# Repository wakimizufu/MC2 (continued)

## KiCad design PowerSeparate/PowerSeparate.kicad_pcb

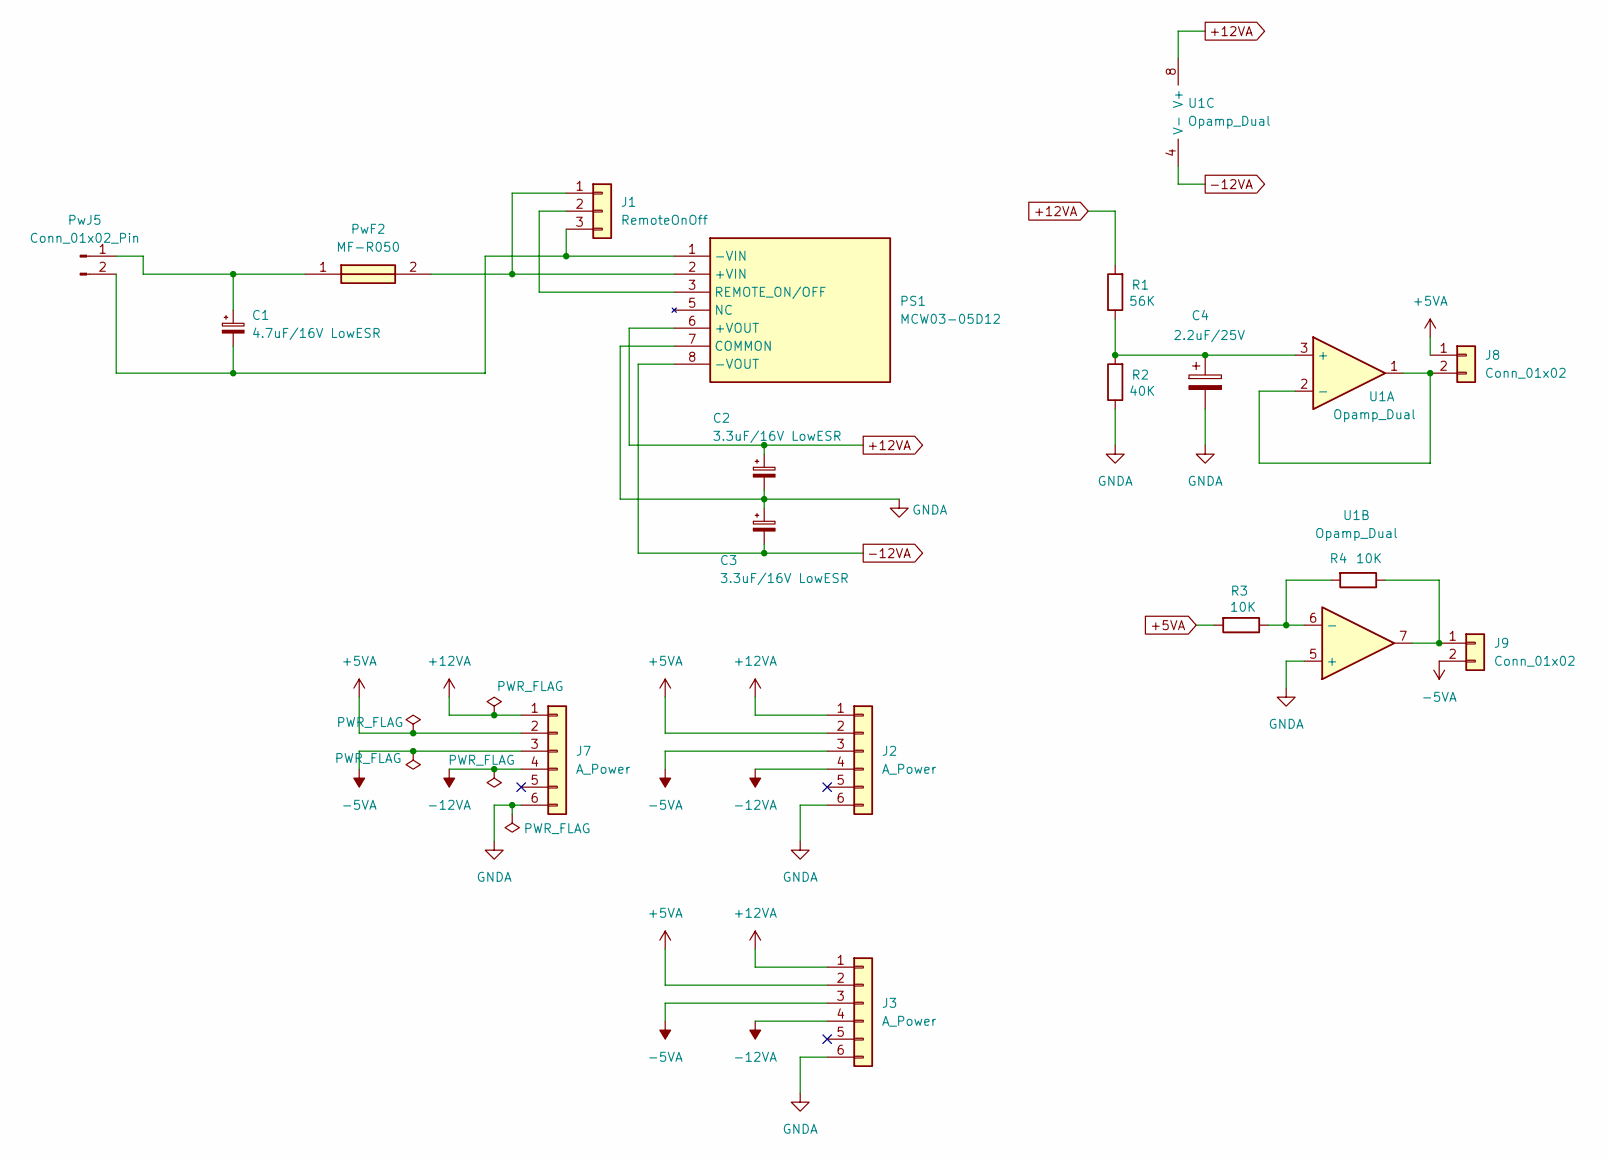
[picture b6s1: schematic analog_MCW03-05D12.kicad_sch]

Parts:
C1: 4.7uF/16V LowESR; CP_Radial_D5.0mm_P2.50mm
C2, C3: 3.3uF/16V LowESR; CP_Radial_D5.0mm_P2.50mm
C4: 2.2uF/25V; CP_Radial_D5.0mm_P2.50mm
J1: RemoteOnOff; PinSocket_1x03_P2.54mm_Vertical
J2, J3, J7: A_Power; PinHeader_1x06_P2.54mm_Vertical
J8, J9: Conn_01x02; PinHeader_1x02_P2.54mm_Vertical
PS1: MCW03-05D12; MCW0305D12; Manufacturer_Part_Number MCW03-05D12
PwF2: MF-R050; MFR050; Manufacturer_Part_Number MF-R050; Mouser Part Number 652-MFR050
PwJ5: Conn_01x02_Pin; PinHeader_1x02_P2.54mm_Vertical
R1: 56K; R_Axial_DIN0207_L6.3mm_D2.5mm_P2.54mm_Vertical
R2: 40K; R_Axial_DIN0207_L6.3mm_D2.5mm_P2.54mm_Vertical
R3, R4: 10K; R_Axial_DIN0207_L6.3mm_D2.5mm_P2.54mm_Vertical
U1: Opamp_Dual; SOIC-8_3.9x4.9mm_P1.27mm

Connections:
+5VA: J2.2, J3.2, J7.2, J8.1, R3.2
+12VA: C2.1, J2.1, J3.1, J7.1, PS1.6 (+VOUT), R1.2, U1.8 (V+)
-5VA: J2.3, J3.3, J7.3, J9.2
-12VA: C3.2, J2.4, J3.4, J7.4, PS1.8 (-VOUT), U1.4 (V-)
GNDA: C2.2, C3.1, C4.2, J2.6, J3.6, J7.6, PS1.7 (COMMON), R2.1, U1.5 (+)
unnamed: J1.1, PS1.2 (+VIN), PwF2.2
unnamed: J1.2, PS1.3 (REMOTE_ON/OFF)
unnamed: C1.2, J1.3, PS1.1 (-VIN), PwJ5.2
unnamed: J8.2, U1.1, U1.2 (-)
unnamed: J9.1, R4.1, U1.7
unnamed: C1.1, PwF2.1, PwJ5.1
unnamed: C4.1, R1.1, R2.2, U1.3 (+)
unnamed: R3.1, R4.2, U1.6 (-)

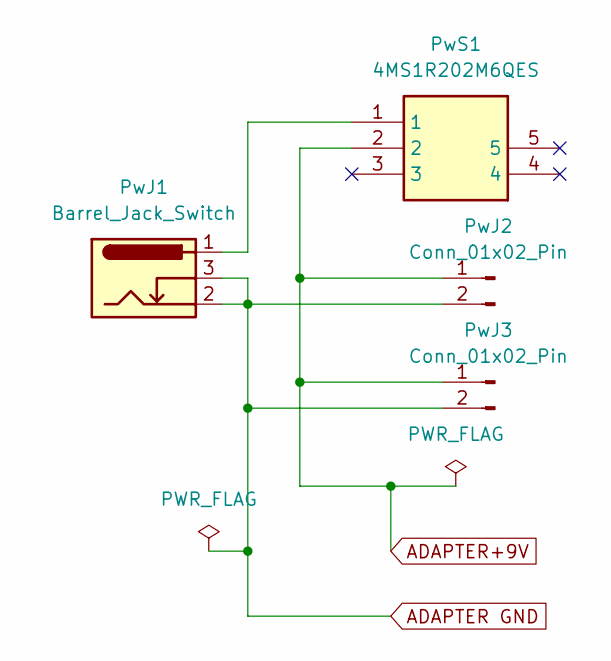
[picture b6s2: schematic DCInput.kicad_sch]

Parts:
PwJ1: Barrel_Jack_Switch; BarrelJack_Horizontal
PwJ2, PwJ3: Conn_01x02_Pin; PinHeader_1x02_P2.54mm_Vertical
PwS1: 4MS1R202M6QES; Manufacturer_Part_Number 4MS1R202M6QES

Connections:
ADAPTER GND: PwJ1.2, PwJ1.3, PwJ2.2, PwJ3.2
ADAPTER+9V: PwJ2.1, PwJ3.1, PwS1.2
unnamed: PwJ1.1, PwS1.1

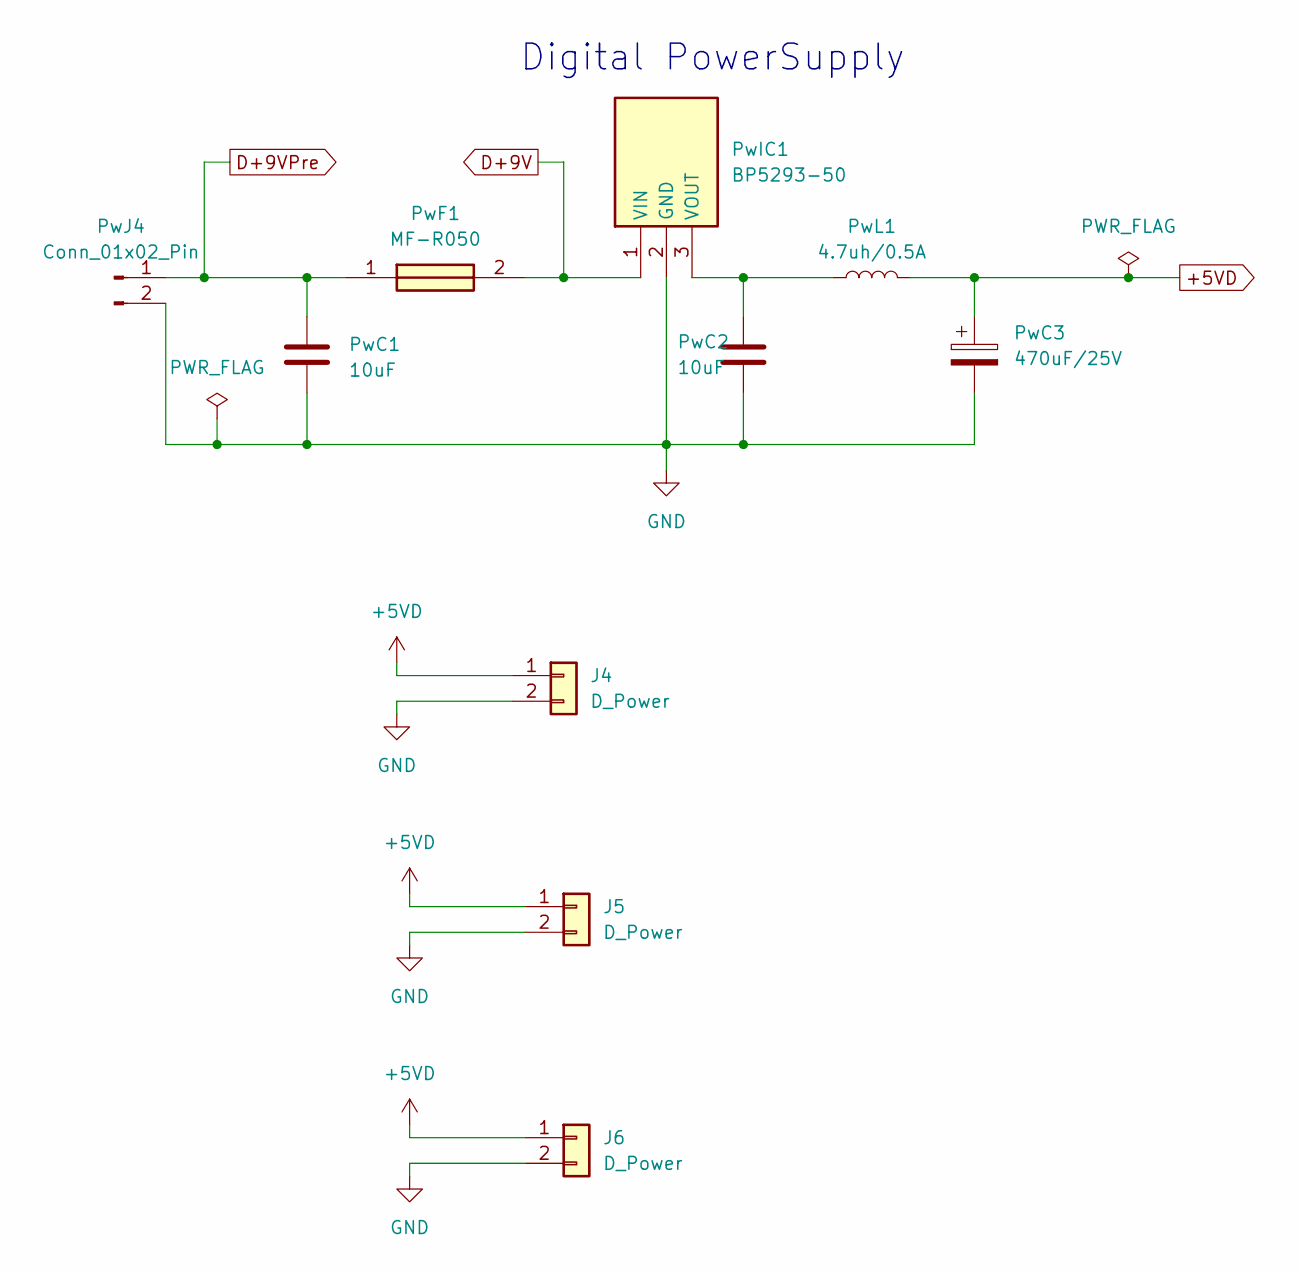
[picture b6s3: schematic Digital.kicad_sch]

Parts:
J4, J5, J6: D_Power; PinSocket_1x02_P2.54mm_Vertical
PwC1, PwC2: 10uF; C_Disc_D5.1mm_W3.2mm_P5.00mm
PwC3: 470uF/25V; CP_Radial_D5.0mm_P2.50mm
PwF1: MF-R050; MFR050; Manufacturer_Part_Number MF-R050; Mouser Part Number 652-MFR050
PwIC1: BP5293-50; TO254P570X1700X1780-3P; Manufacturer_Part_Number BP5293-50; Mouser Part Number 755-BP5293-50
PwJ4: Conn_01x02_Pin; PinHeader_1x02_P2.54mm_Vertical
PwL1: 4.7uh/0.5A; R_Axial_DIN0207_L6.3mm_D2.5mm_P7.62mm_Horizontal

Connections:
+5VD: J4.1, J5.1, J6.1, PwC3.1, PwL1.2
D+9V: PwF1.2, PwIC1.1 (VIN)
D+9VPre: PwC1.1, PwF1.1, PwJ4.1
GND: J4.2, J5.2, J6.2, PwC1.2, PwC2.2, PwC3.2, PwIC1.2 (GND), PwJ4.2
unnamed: PwC2.1, PwIC1.3 (VOUT), PwL1.1

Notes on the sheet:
Digital PowerSupply

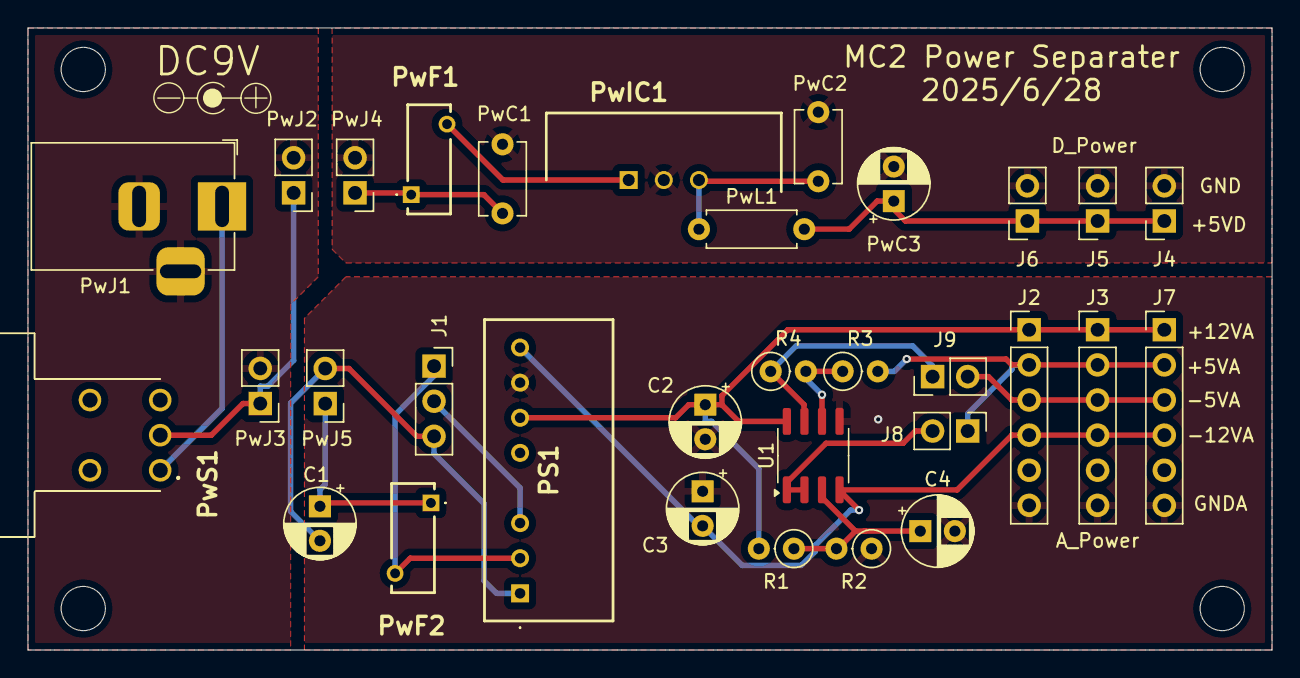
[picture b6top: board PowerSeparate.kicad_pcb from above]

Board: 2 copper layers, 90.0 x 45.0 mm, 32 parts (0 on the bottom side), 21 nets.

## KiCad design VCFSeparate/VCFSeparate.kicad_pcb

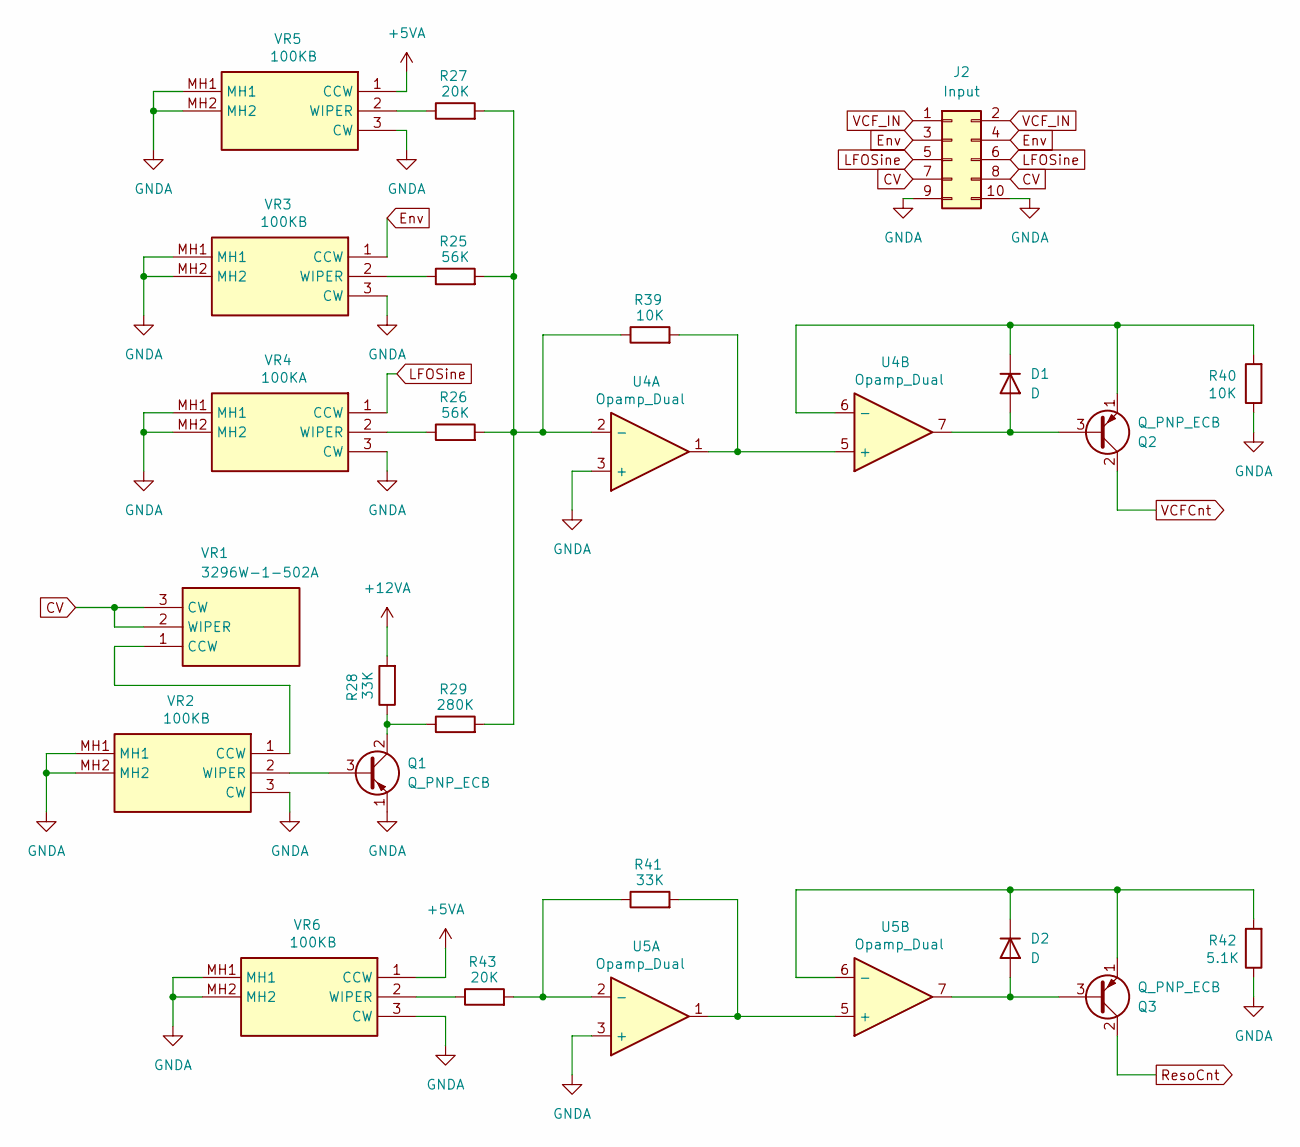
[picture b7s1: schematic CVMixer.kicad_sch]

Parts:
D1, D2: D; D_DO-35_SOD27_P2.54mm_Vertical_AnodeUp
J2: Input; PinSocket_2x05_P2.54mm_Vertical
Q1, Q2, Q3: Q_PNP_ECB; TO-92_HandSolder
R25, R26: 56K; R_Axial_DIN0204_L3.6mm_D1.6mm_P2.54mm_Vertical
R27, R43: 20K; R_Axial_DIN0204_L3.6mm_D1.6mm_P2.54mm_Vertical
R28, R41: 33K; R_Axial_DIN0204_L3.6mm_D1.6mm_P2.54mm_Vertical
R29: 280K; R_Axial_DIN0204_L3.6mm_D1.6mm_P2.54mm_Vertical
R39, R40: 10K; R_Axial_DIN0204_L3.6mm_D1.6mm_P2.54mm_Vertical
R42: 5.1K; R_Axial_DIN0204_L3.6mm_D1.6mm_P2.54mm_Vertical
U4, U5: Opamp_Dual; SO-8_3.9x4.9mm_P1.27mm
VR1: 3296W-1-502A; 3296W1502A; Manufacturer_Part_Number 3296W-1-502A; Mouser Part Number 652-3296W-1-502A
VR2, VR3, VR5, VR6: 100KB; RK09D117000B; Manufacturer_Part_Number RK09D117000B; Mouser Part Number 688-RK09D117000B
VR4: 100KA; RK09D117000B; Manufacturer_Part_Number RK09D117000B; Mouser Part Number 688-RK09D117000B

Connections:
+5VA: VR5.1 (CCW), VR6.1 (CCW); also elsewhere on the board
+12VA: R28.2; also elsewhere on the board
CV: J2.7, J2.8, VR1.2 (WIPER), VR1.3 (CW)
FilterEnv: J2.3, J2.4, VR3.1 (CCW)
LFOSine: J2.5, J2.6, VR4.1 (CCW)
unnamed: D1.2 (A), Q2.3 (B), U4.7
unnamed: D1.1 (K), Q2.1 (E), R40.2, U4.6 (-)
unnamed: D2.2 (A), Q3.3 (B), U5.7
unnamed: D2.1 (K), Q3.1 (E), R42.2, U5.6 (-)
unnamed: Q1.3 (B), VR2.2 (WIPER)
unnamed: Q1.2 (C), R28.1, R29.1
unnamed: R25.2, R26.2, R27.2, R29.2, R39.1, U4.2 (-)
unnamed: R39.2, U4.1, U4.5 (+)
unnamed: R41.1, R43.2, U5.2 (-)
unnamed: R41.2, U5.1, U5.5 (+)
unnamed: VR1.1 (CCW), VR2.1 (CCW)
unnamed: R25.1, VR3.2 (WIPER)
unnamed: R26.1, VR4.2 (WIPER)
unnamed: R27.1, VR5.2 (WIPER)
unnamed: R43.1, VR6.2 (WIPER)
ResoCnt: Q3.2 (C); also elsewhere on the board
VCFCnt: Q2.2 (C); also elsewhere on the board
VCF_IN: J2.1, J2.2; also elsewhere on the board

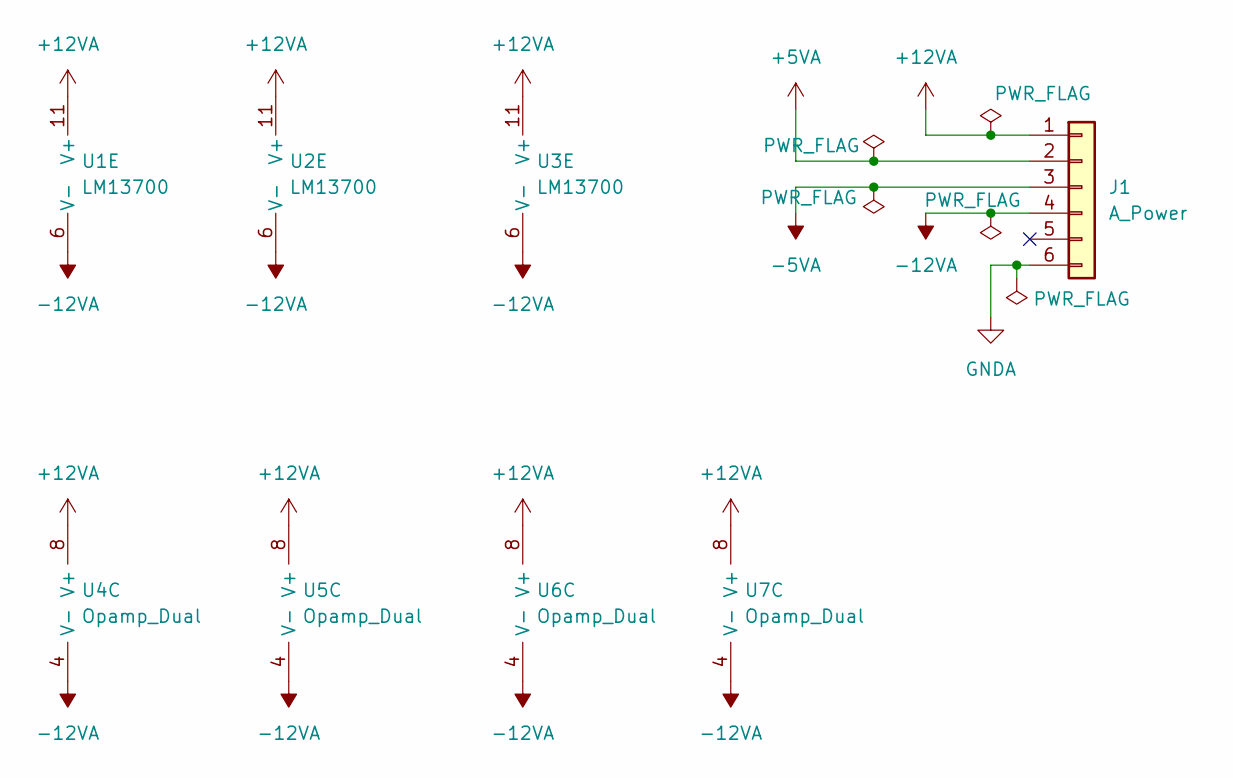
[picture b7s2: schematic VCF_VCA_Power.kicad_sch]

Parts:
J1: A_Power; PinHeader_1x06_P2.54mm_Vertical
U1, U3: LM13700; SOIC-16_3.9x9.9mm_P1.27mm
U2: LM13700
U4, U5, U6, U7: Opamp_Dual; SO-8_3.9x4.9mm_P1.27mm

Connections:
+5VA: J1.2; also elsewhere on the board
+12VA: J1.1, U1.11 (V+), U2.11 (V+), U3.11 (V+), U4.8 (V+), U5.8 (V+), U6.8 (V+), U7.8 (V+); also elsewhere on the board
-5VA: J1.3
-12VA: J1.4, U1.6 (V-), U2.6 (V-), U3.6 (V-), U4.4 (V-), U5.4 (V-), U6.4 (V-), U7.4 (V-); also elsewhere on the board

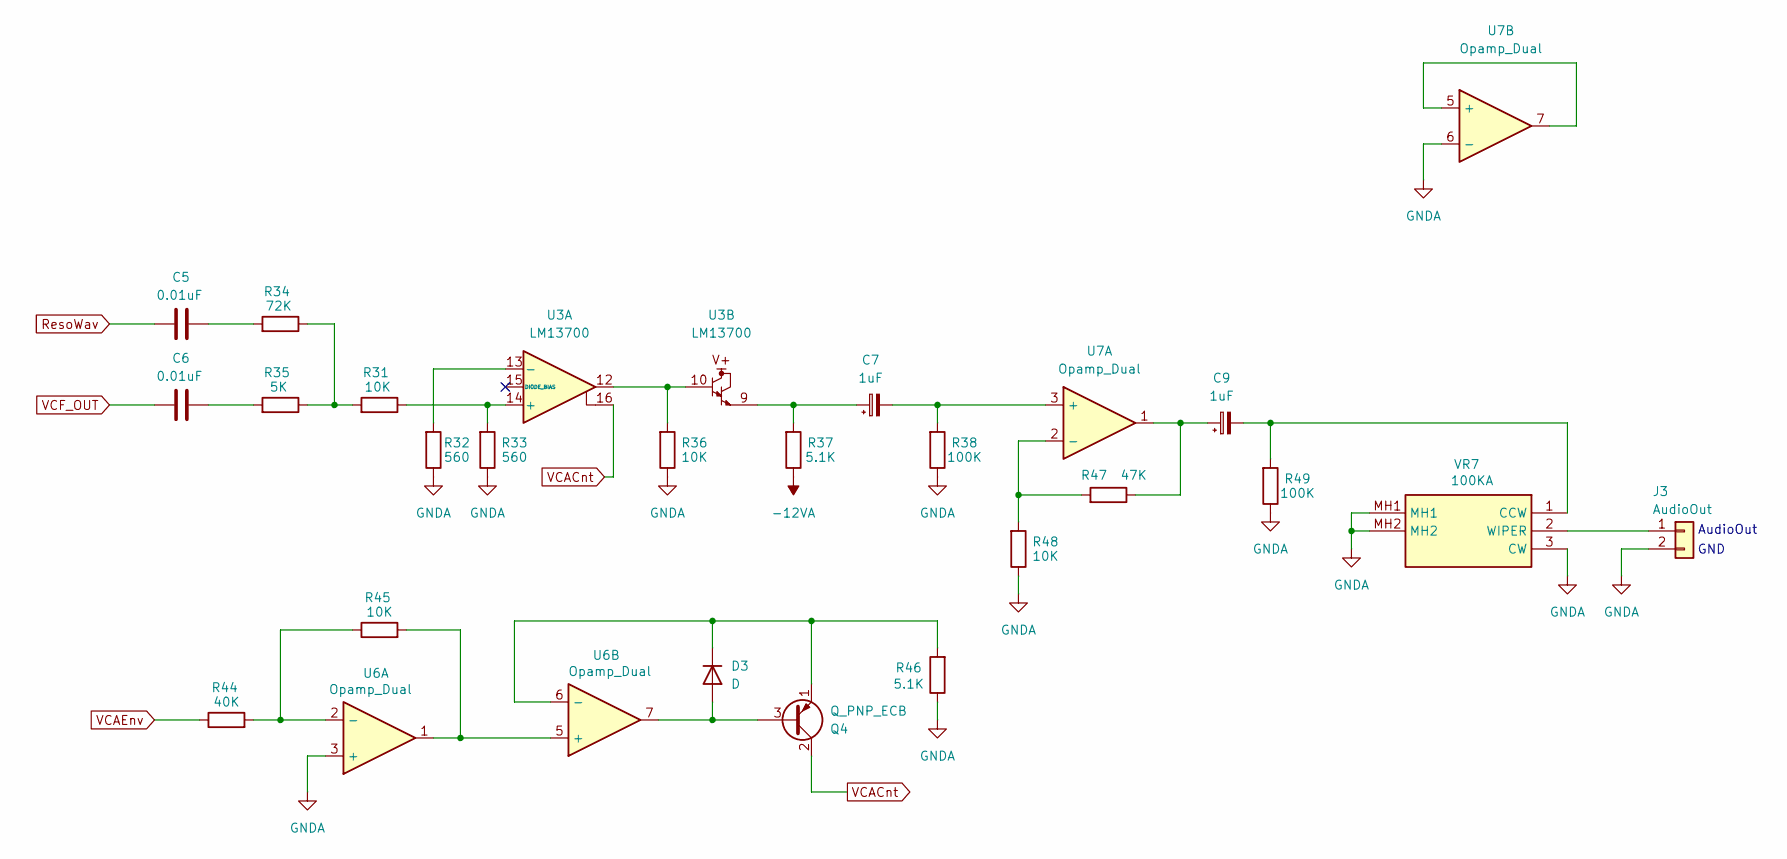
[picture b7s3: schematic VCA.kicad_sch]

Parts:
C5, C6: 0.01uF; C_Disc_D3.4mm_W2.1mm_P2.50mm
C7, C9: 1uF; CP_Radial_D5.0mm_P2.50mm
D3: D; D_DO-35_SOD27_P2.54mm_Vertical_AnodeUp
J3: AudioOut; PinHeader_1x02_P2.54mm_Vertical
Q4: Q_PNP_ECB; TO-92_HandSolder
R31, R36, R45, R48: 10K; R_Axial_DIN0204_L3.6mm_D1.6mm_P2.54mm_Vertical
R32, R33: 560; R_Axial_DIN0204_L3.6mm_D1.6mm_P2.54mm_Vertical
R34: 72K; R_Axial_DIN0204_L3.6mm_D1.6mm_P2.54mm_Vertical
R35: 5K; R_Axial_DIN0204_L3.6mm_D1.6mm_P2.54mm_Vertical
R37, R46: 5.1K; R_Axial_DIN0204_L3.6mm_D1.6mm_P2.54mm_Vertical
R38, R49: 100K; R_Axial_DIN0204_L3.6mm_D1.6mm_P2.54mm_Vertical
R44: 40K; R_Axial_DIN0204_L3.6mm_D1.6mm_P2.54mm_Vertical
R47: 47K; R_Axial_DIN0204_L3.6mm_D1.6mm_P2.54mm_Vertical
U3: LM13700; SOIC-16_3.9x9.9mm_P1.27mm
U6, U7: Opamp_Dual; SO-8_3.9x4.9mm_P1.27mm
VR7: 100KA; RK09D117000B; Manufacturer_Part_Number RK09D117000B; Mouser Part Number 688-RK09D117000B

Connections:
-12VA: R37.1; also elsewhere on the board
unnamed: C5.2, R34.2
unnamed: C6.2, R35.2
unnamed: C7.1, R37.2, U3.9
unnamed: C9.1, R47.1, U7.1
unnamed: D3.2 (A), Q4.3 (B), U6.7
unnamed: D3.1 (K), Q4.1 (E), R46.2, U6.6 (-)
unnamed: J3.1, VR7.2 (WIPER)
unnamed: R31.2, R34.1, R35.1
unnamed: R36.2, U3.10, U3.12
unnamed: R31.1, R33.2, U3.14 (+)
unnamed: R32.2, U3.13 (-)
unnamed: R44.2, R45.1, U6.2 (-)
unnamed: R45.2, U6.1, U6.5 (+)
unnamed: C7.2, R38.2, U7.3 (+)
unnamed: R47.2, R48.2, U7.2 (-)
unnamed: U7.5 (+), U7.7
unnamed: C9.2, R49.2, VR7.1 (CCW)
ResoWav: C5.1; also elsewhere on the board
VCACnt: Q4.2 (C), U3.16
VCF_OUT: C6.1; also elsewhere on the board

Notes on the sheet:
GND
AudioOut

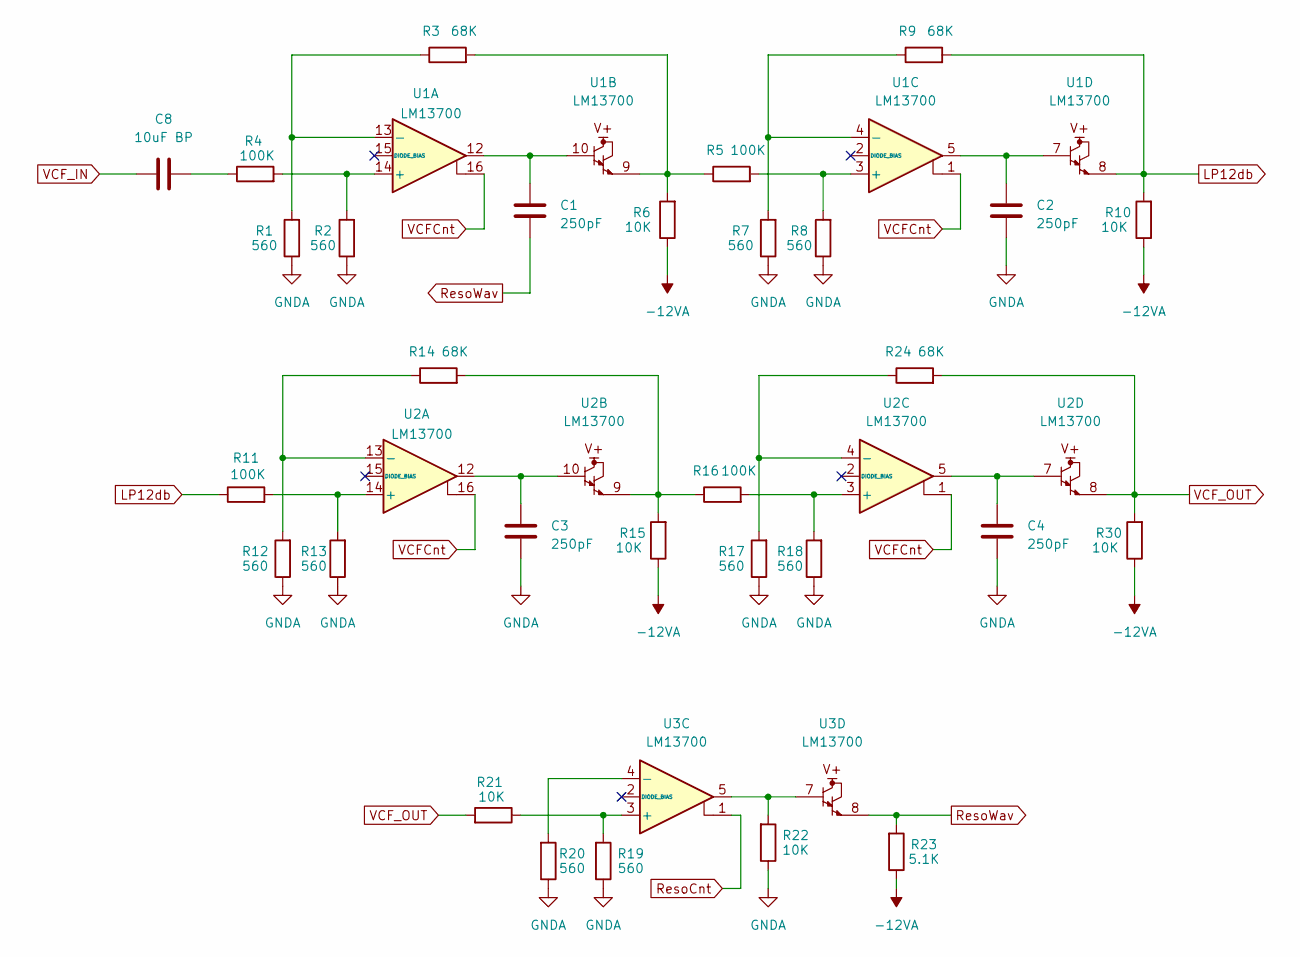
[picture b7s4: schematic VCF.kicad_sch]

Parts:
C1, C2, C3, C4: 250pF; C_Disc_D3.4mm_W2.1mm_P2.50mm
C8: 10uF BP; C_Radial_D5.0mm_H5.0mm_P2.00mm
R1, R2, R7, R8, R12, R13, R17, R18, R19, R20: 560; R_Axial_DIN0204_L3.6mm_D1.6mm_P2.54mm_Vertical
R3, R9, R14, R24: 68K; R_Axial_DIN0204_L3.6mm_D1.6mm_P2.54mm_Vertical
R4, R5, R11, R16: 100K; R_Axial_DIN0204_L3.6mm_D1.6mm_P2.54mm_Vertical
R6, R10, R15, R21, R22, R30: 10K; R_Axial_DIN0204_L3.6mm_D1.6mm_P2.54mm_Vertical
R23: 5.1K; R_Axial_DIN0204_L3.6mm_D1.6mm_P2.54mm_Vertical
U1, U3: LM13700; SOIC-16_3.9x9.9mm_P1.27mm
U2: LM13700

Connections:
-12VA: R6.1, R10.1, R15.1, R23.1, R30.1; also elsewhere on the board
LP12db: R9.2, R10.2, R11.1, U1.8
unnamed: C1.1, U1.10, U1.12
unnamed: C2.1, U1.5, U1.7
unnamed: C3.1, U2.10, U2.12
unnamed: C4.1, U2.5, U2.7
unnamed: C8.2, R4.1
unnamed: R3.2, R5.1, R6.2, U1.9
unnamed: R14.2, R15.2, R16.1, U2.9
unnamed: R22.2, U3.5, U3.7
unnamed: R2.2, R4.2, U1.14 (+)
unnamed: R1.2, R3.1, U1.13 (-)
unnamed: R5.2, R8.2, U1.3 (+)
unnamed: R7.2, R9.1, U1.4 (-)
unnamed: R11.2, R13.2, U2.14 (+)
unnamed: R12.2, R14.1, U2.13 (-)
unnamed: R16.2, R18.2, U2.3 (+)
unnamed: R17.2, R24.1, U2.4 (-)
unnamed: R19.2, R21.1, U3.3 (+)
unnamed: R20.2, U3.4 (-)
ResoCnt: U3.1; also elsewhere on the board
ResoWav: C1.2, R23.2, U3.8; also elsewhere on the board
VCFCnt: U1.1, U1.16, U2.1, U2.16; also elsewhere on the board
VCF_IN: C8.1; also elsewhere on the board
VCF_OUT: R21.2, R24.2, R30.2, U2.8; also elsewhere on the board

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
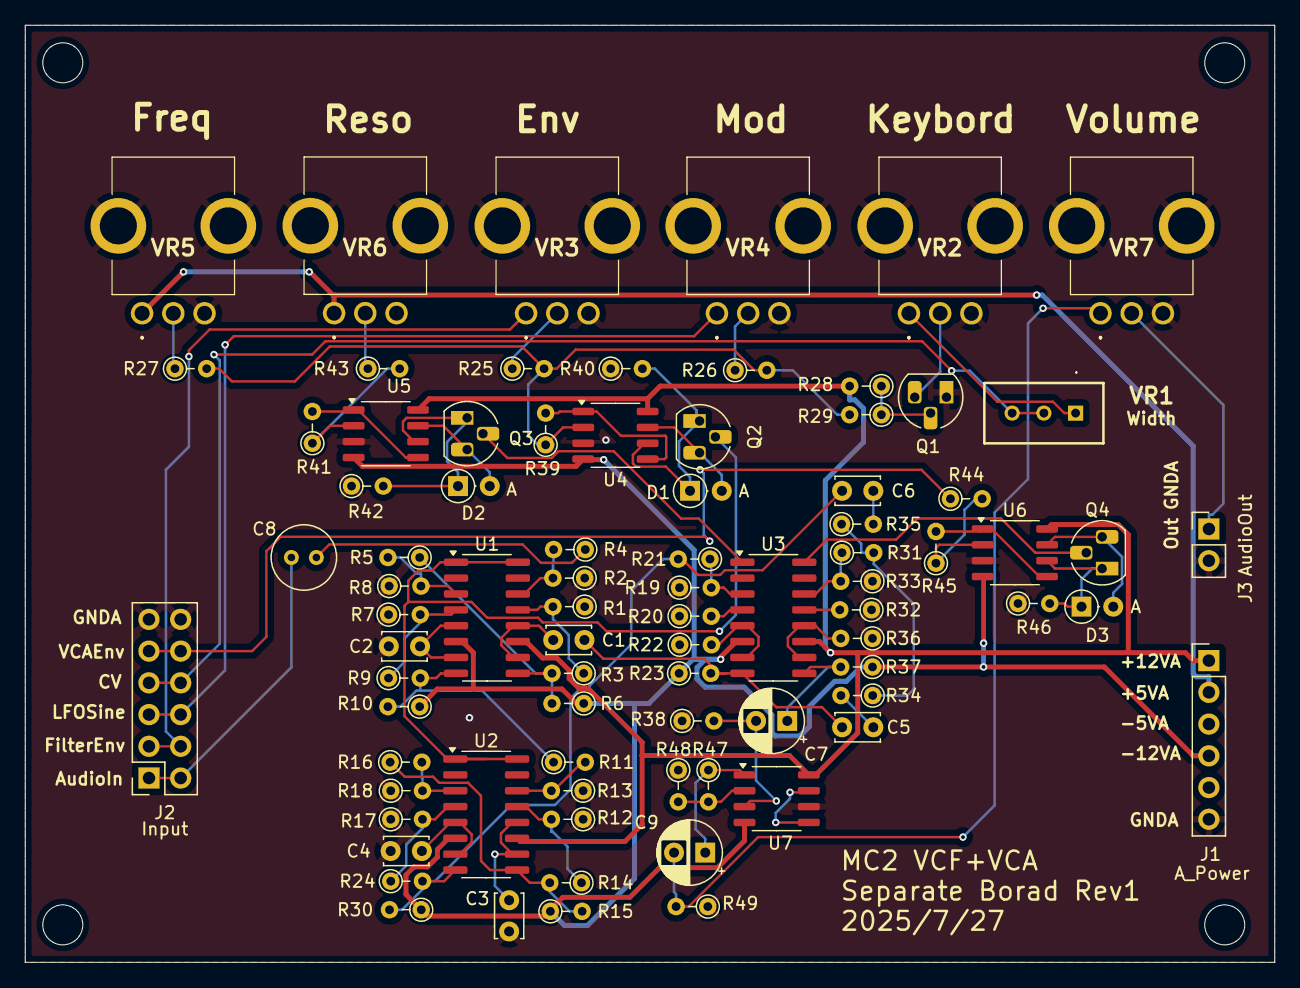
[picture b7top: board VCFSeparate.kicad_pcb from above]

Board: 2 copper layers, 100.0 x 75.0 mm, 82 parts (0 on the bottom side), 65 nets.

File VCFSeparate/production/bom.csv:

Designator,Footprint,Quantity,Value,LCSC Part #
"C1, C2, C3, C4",C_Disc_D3.4mm_W2.1mm_P2.50mm,4,250pF,
"C5, C6",C_Disc_D3.4mm_W2.1mm_P2.50mm,2,0.01uF,
"C7, C9",CP_Radial_D5.0mm_P2.50mm,2,1uF,
C8,C_Radial_D5.0mm_H5.0mm_P2.00mm,1,10uF BP,
"D1, D2, D3",D_DO-35_SOD27_P2.54mm_Vertical_AnodeUp,3,D,
J1,PinHeader_1x06_P2.54mm_Vertical,1,A_Power,
J2,PinSocket_2x05_P2.54mm_Vertical,1,Input,
J3,PinHeader_1x02_P2.54mm_Vertical,1,AudioOut,
"Q1, Q2, Q3, Q4",TO-92_HandSolder,4,Q_PNP_ECB,
"R1, R12, R13, R17, R18, R19, R2, R20, R32, R33, R7, R8",R_Axial_DIN0204_L3.6mm_D1.6mm_P2.54mm_Vertical,12,560,
"R10, R15, R21, R22, R30, R31, R36, R39, R40, R45, R48, R6",R_Axial_DIN0204_L3.6mm_D1.6mm_P2.54mm_Vertical,12,10K,
"R11, R16, R38, R4, R49, R5",R_Axial_DIN0204_L3.6mm_D1.6mm_P2.54mm_Vertical,6,100K,
"R14, R24, R3, R9",R_Axial_DIN0204_L3.6mm_D1.6mm_P2.54mm_Vertical,4,68K,
"R23, R37, R42, R46",R_Axial_DIN0204_L3.6mm_D1.6mm_P2.54mm_Vertical,4,5.1K,
"R25, R26",R_Axial_DIN0204_L3.6mm_D1.6mm_P2.54mm_Vertical,2,56K,
"R27, R43",R_Axial_DIN0204_L3.6mm_D1.6mm_P2.54mm_Vertical,2,20K,
"R28, R41",R_Axial_DIN0204_L3.6mm_D1.6mm_P2.54mm_Vertical,2,33K,
R29,R_Axial_DIN0204_L3.6mm_D1.6mm_P2.54mm_Vertical,1,280K,
R34,R_Axial_DIN0204_L3.6mm_D1.6mm_P2.54mm_Vertical,1,72K,
R35,R_Axial_DIN0204_L3.6mm_D1.6mm_P2.54mm_Vertical,1,5K,
R44,R_Axial_DIN0204_L3.6mm_D1.6mm_P2.54mm_Vertical,1,40K,
R47,R_Axial_DIN0204_L3.6mm_D1.6mm_P2.54mm_Vertical,1,47K,
"U1, U2, U3",SOIC-16_3.9x9.9mm_P1.27mm,3,LM13700,
"U4, U5, U6, U7",SO-8_3.9x4.9mm_P1.27mm,4,Opamp_Dual,
VR1,3296W1502A,1,3296W-1-502A,
"VR2, VR3, VR5, VR6",RK09D117000B,4,100KB,
"VR4, VR7",RK09D117000B,2,100KA,
